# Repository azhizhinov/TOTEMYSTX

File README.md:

# TOTEMYSTX
TOTEMYSTX is a 38-40 keys column-staggered split keyboard. It meant to be used with a Seed Studio XIAO RP2040 or nRF52840.
TOTEMYSTX is a replica of the famous TOTEM by GEIGEIGEIST for MX spacing (19.05x19.05mm) switches like Cherry MX.

**Warning. I don't have printed PCBs on hands, so can't check or debug. It should work in theory. Use this files on youre own risk.**

https://github.com/GEIGEIGEIST/TOTEM

TOTEMYSTX with 38 keys shares the same firmware as of the original TOTEM.

There are 3 mods for the TOTEMYSTX use cases.

The jumper is open. 38 keys as usual, but the right thumb key not in use, has no connection to the MCU.

If you'll cut out the outer thumb key, you have to solder the jumper in "TOTEMX" mode. It's will be classical TOTEM/TOTEMX.

To use all 40 keys, you have to solder the jumper in "TOTEMYSTX" mode and change a keymap and recompile then.

TOTEMX with 38 keys shares the same firmware as of the original TOTEM.

Cases's models are designed to use M2 screws. For the TOTEMYSTX case use M2\*10mm -8pcs and M2\*8mm -2pcs and M2\*10mm -8pcs for the TOTEMX case.

The cases and PCBs are not compatible with the previous version. https://github.com/azhizhinov/TOTEMX

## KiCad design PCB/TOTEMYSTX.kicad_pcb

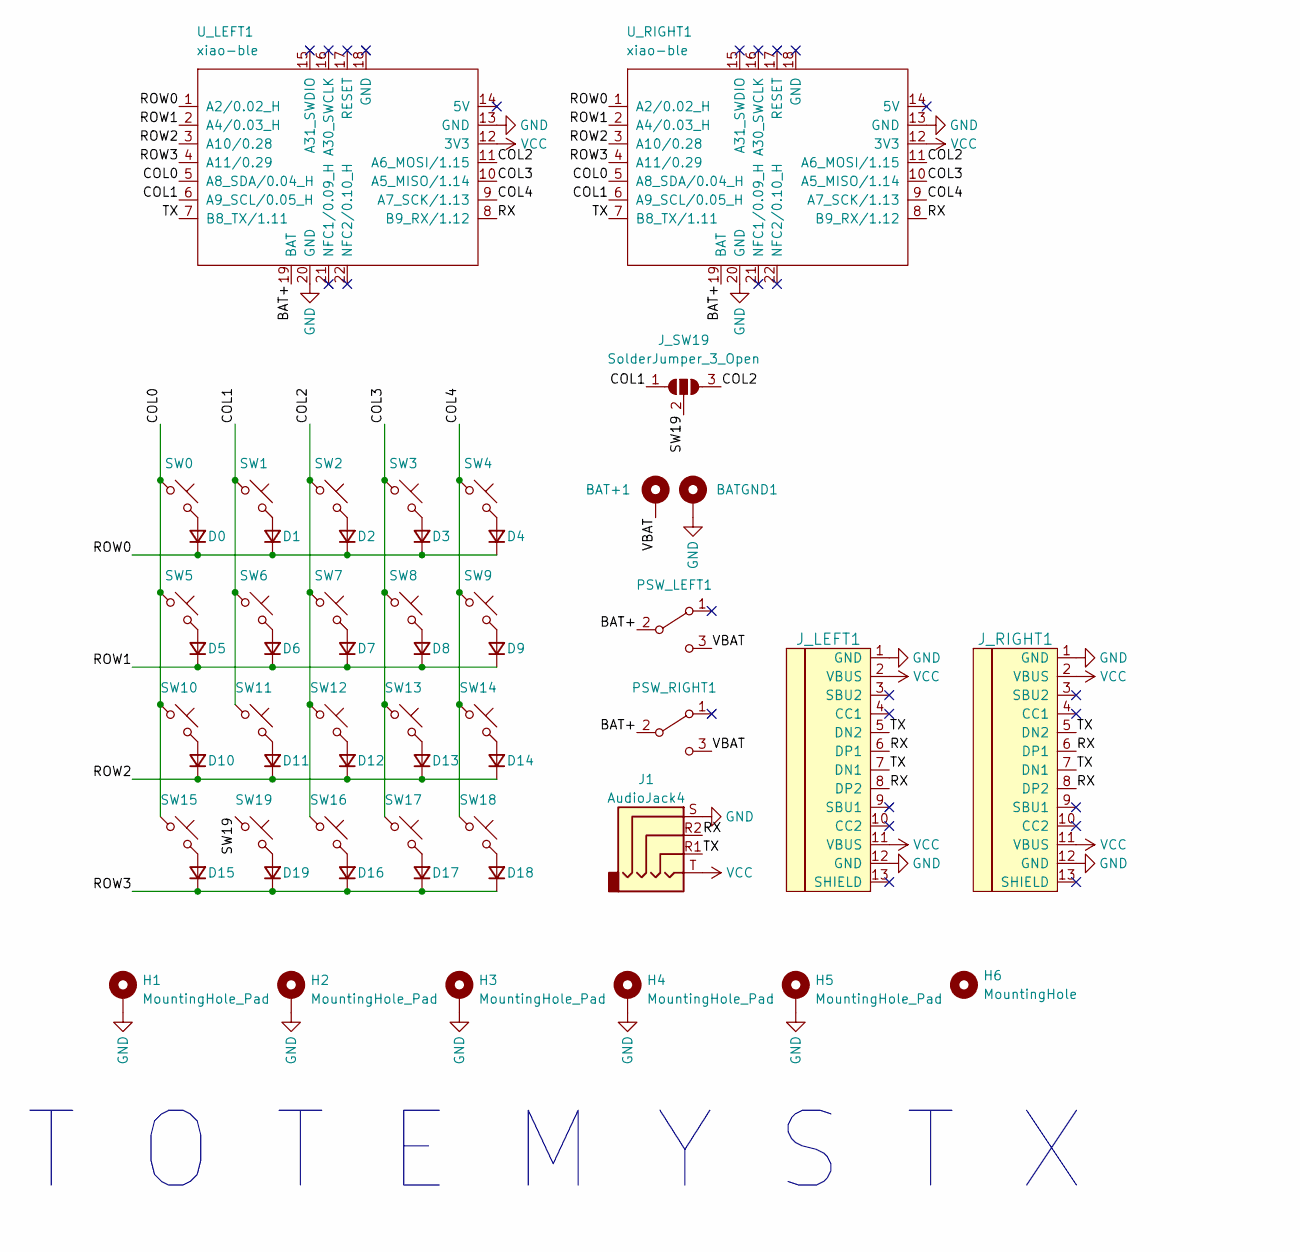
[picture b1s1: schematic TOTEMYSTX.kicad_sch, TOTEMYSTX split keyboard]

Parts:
BAT+1: +; BatteryPad
BATGND1: -; BatteryPad
D0, D1, D2, D3, D4, D5, D6, D7, D8, D9, D10, D11, D12, D13, D14, D15, D16, D17, D18, D19: D_Small; TOTEMYSTX-D
H1, H2, H3, H4, H5: MountingHole_Pad; TOTEMYSTX-MountingHole_3.2mm_M3_DIN965_Pad
H6: MountingHole; TOTEMYSTX-BREAKWAY
J1: AudioJack4; TOTEMYSTX-TRRS-THT
J_LEFT1: HRO-TYPE-C-31-M-12; TOTEMYSTX-TYPE-C
J_RIGHT1: HRO-TYPE-C-31-M-12; TOTEMYSTX-TYPE-C
J_SW19: SolderJumper_3_Open; TOTEMYSTX-SolderJumper-3_P1.3mm_Open_RoundedPad1.0x1.5mm
PSW_LEFT1: SW_SPDT; TOTEMYSTX-SW_SPDT_PCM12
PSW_RIGHT1: SW_SPDT; TOTEMYSTX-SW_SPDT_PCM12
SW0, SW1, SW2, SW3, SW4, SW5, SW6, SW7, SW8, SW9, SW10, SW11, SW12, SW13, SW14, SW15, SW16, SW17, SW18, SW19: SW_Push_45deg; TOTEMYSTX-KEY
U_LEFT1: xiao-ble; TOTEMYSTX-XIAO-BLE-SMD
U_RIGHT1: xiao-ble; TOTEMYSTX-XIAO-BLE-SMD

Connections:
/BAT+: PSW_LEFT1.2 (B), PSW_RIGHT1.2 (B), U_LEFT1.19 (BAT), U_RIGHT1.19 (BAT)
/COL0: SW0.1, SW5.1, SW10.1, SW15.1, U_LEFT1.5 (A8_SDA/0.04_H), U_RIGHT1.5 (A8_SDA/0.04_H)
/COL1: J_SW19.1 (A), SW1.1, SW6.1, SW11.1, U_LEFT1.6 (A9_SCL/0.05_H), U_RIGHT1.6 (A9_SCL/0.05_H)
/COL2: J_SW19.3 (B), SW2.1, SW7.1, SW12.1, SW16.1, U_LEFT1.11 (A6_MOSI/1.15), U_RIGHT1.11 (A6_MOSI/1.15)
/COL3: SW3.1, SW8.1, SW13.1, SW17.1, U_LEFT1.10 (A5_MISO/1.14), U_RIGHT1.10 (A5_MISO/1.14)
/COL4: SW4.1, SW9.1, SW14.1, SW18.1, U_LEFT1.9 (A7_SCK/1.13), U_RIGHT1.9 (A7_SCK/1.13)
/ROW0: D0.1 (K), D1.1 (K), D2.1 (K), D3.1 (K), D4.1 (K), U_LEFT1.1 (A2/0.02_H), U_RIGHT1.1 (A2/0.02_H)
/ROW1: D5.1 (K), D6.1 (K), D7.1 (K), D8.1 (K), D9.1 (K), U_LEFT1.2 (A4/0.03_H), U_RIGHT1.2 (A4/0.03_H)
/ROW2: D10.1 (K), D11.1 (K), D12.1 (K), D13.1 (K), D14.1 (K), U_LEFT1.3 (A10/0.28), U_RIGHT1.3 (A10/0.28)
/ROW3: D15.1 (K), D16.1 (K), D17.1 (K), D18.1 (K), D19.1 (K), U_LEFT1.4 (A11/0.29), U_RIGHT1.4 (A11/0.29)
/RX: J1.R2, J_LEFT1.6 (DP1), J_LEFT1.8 (DP2), J_RIGHT1.6 (DP1), J_RIGHT1.8 (DP2), U_LEFT1.8 (B9_RX/1.12), U_RIGHT1.8 (B9_RX/1.12)
/SW19: J_SW19.2 (C), SW19.1
/TX: J1.R1, J_LEFT1.5 (DN2), J_LEFT1.7 (DN1), J_RIGHT1.5 (DN2), J_RIGHT1.7 (DN1), U_LEFT1.7 (B8_TX/1.11), U_RIGHT1.7 (B8_TX/1.11)
/VBAT: BAT+1.1, PSW_LEFT1.3 (C), PSW_RIGHT1.3 (C)
GND: BATGND1.1, H1.1, H2.1, H3.1, H4.1, H5.1, J1.S, J_LEFT1.1 (GND), J_LEFT1.12 (GND), J_LEFT1.13 (SHIELD), J_RIGHT1.1 (GND), J_RIGHT1.12 (GND), J_RIGHT1.13 (SHIELD), SW0.GND, SW1.GND, SW2.GND, SW3.GND, SW4.GND, SW5.GND, SW6.GND, SW7.GND, SW8.GND, SW9.GND, SW10.GND, SW11.GND, SW12.GND, SW13.GND, SW14.GND, SW15.GND, SW16.GND, SW17.GND, SW18.GND, SW19.GND, U_LEFT1.13 (GND), U_LEFT1.20 (GND), U_RIGHT1.13 (GND), U_RIGHT1.20 (GND)
unnamed: D0.2 (A), SW0.2
unnamed: D1.2 (A), SW1.2
unnamed: D2.2 (A), SW2.2
unnamed: D3.2 (A), SW3.2
unnamed: D4.2 (A), SW4.2
unnamed: D5.2 (A), SW5.2
unnamed: D6.2 (A), SW6.2
unnamed: D7.2 (A), SW7.2
unnamed: D8.2 (A), SW8.2
unnamed: D9.2 (A), SW9.2
unnamed: D10.2 (A), SW10.2
unnamed: D11.2 (A), SW11.2
unnamed: D12.2 (A), SW12.2
unnamed: D13.2 (A), SW13.2
unnamed: D14.2 (A), SW14.2
unnamed: D15.2 (A), SW15.2
unnamed: D16.2 (A), SW16.2
unnamed: D17.2 (A), SW17.2
unnamed: D18.2 (A), SW18.2
unnamed: D19.2 (A), SW19.2
VCC: J1.T, J_LEFT1.2 (VBUS), J_LEFT1.11 (VBUS), J_RIGHT1.2 (VBUS), J_RIGHT1.11 (VBUS), U_LEFT1.12 (3V3), U_RIGHT1.12 (3V3)

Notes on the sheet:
T O T E M Y S T X

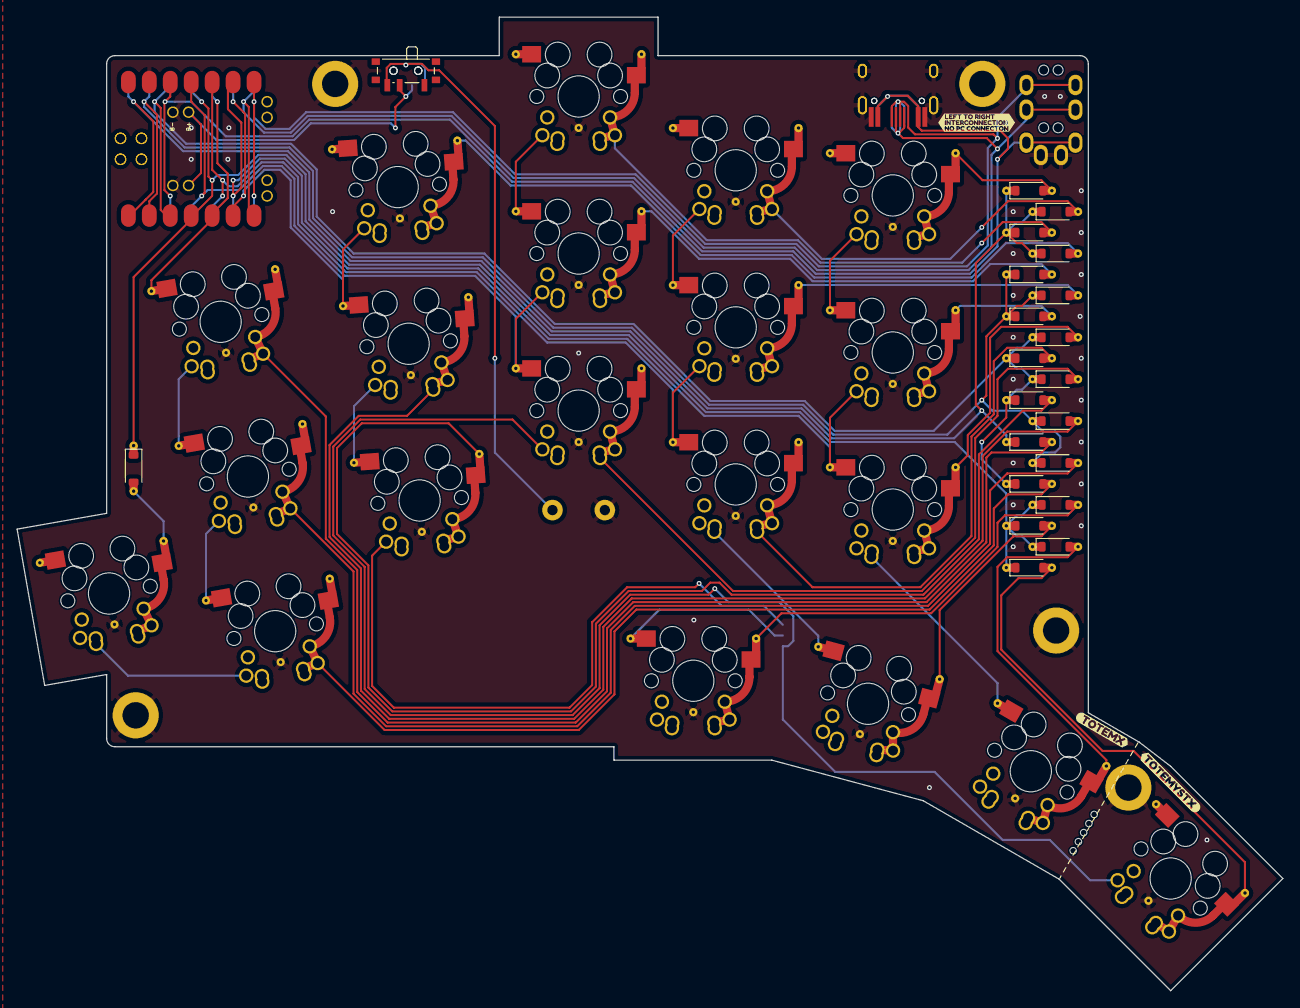
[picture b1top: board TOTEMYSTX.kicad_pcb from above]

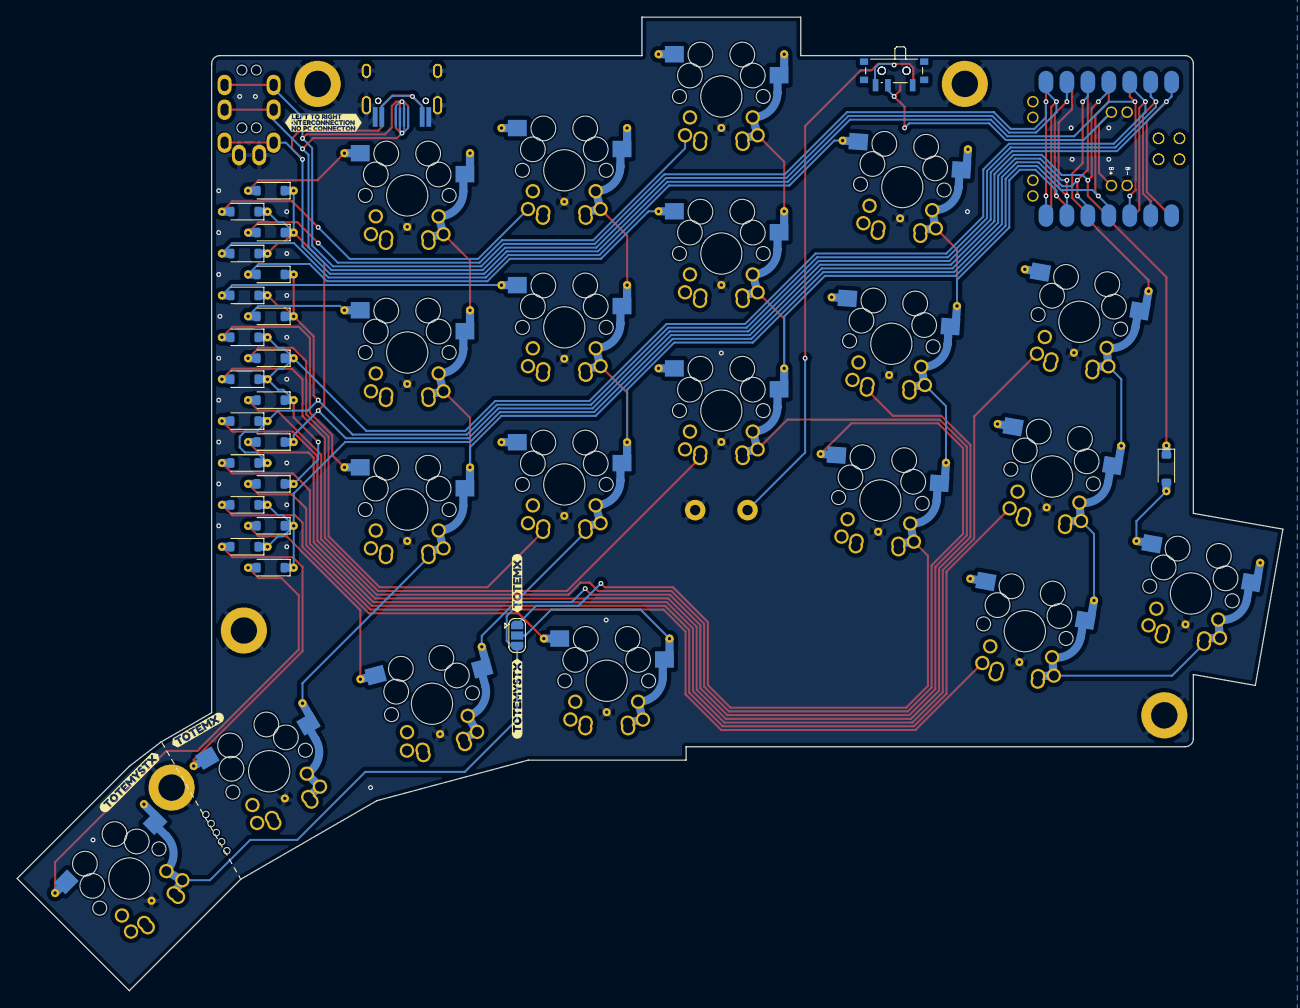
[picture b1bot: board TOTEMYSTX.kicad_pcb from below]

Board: 2 copper layers, 153.5 x 118.1 mm, 64 parts (9 on the bottom side), 36 nets.

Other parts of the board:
kibuzzard-688F7691, kibuzzard-688F7691#2: G***; kibuzzard-688F7691
kibuzzard-68974A0B: G***; kibuzzard-68974A0B
kibuzzard-68974A8D: G***; kibuzzard-68974A8D
kibuzzard-68974A33: G***; kibuzzard-68974A33
kibuzzard-68974A68: G***; kibuzzard-68974A68
kibuzzard-68974C18, kibuzzard-68974C18#2: G***; kibuzzard-68974C18

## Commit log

2025-08-14 Initial upload
2025-08-15 Add gerbers
